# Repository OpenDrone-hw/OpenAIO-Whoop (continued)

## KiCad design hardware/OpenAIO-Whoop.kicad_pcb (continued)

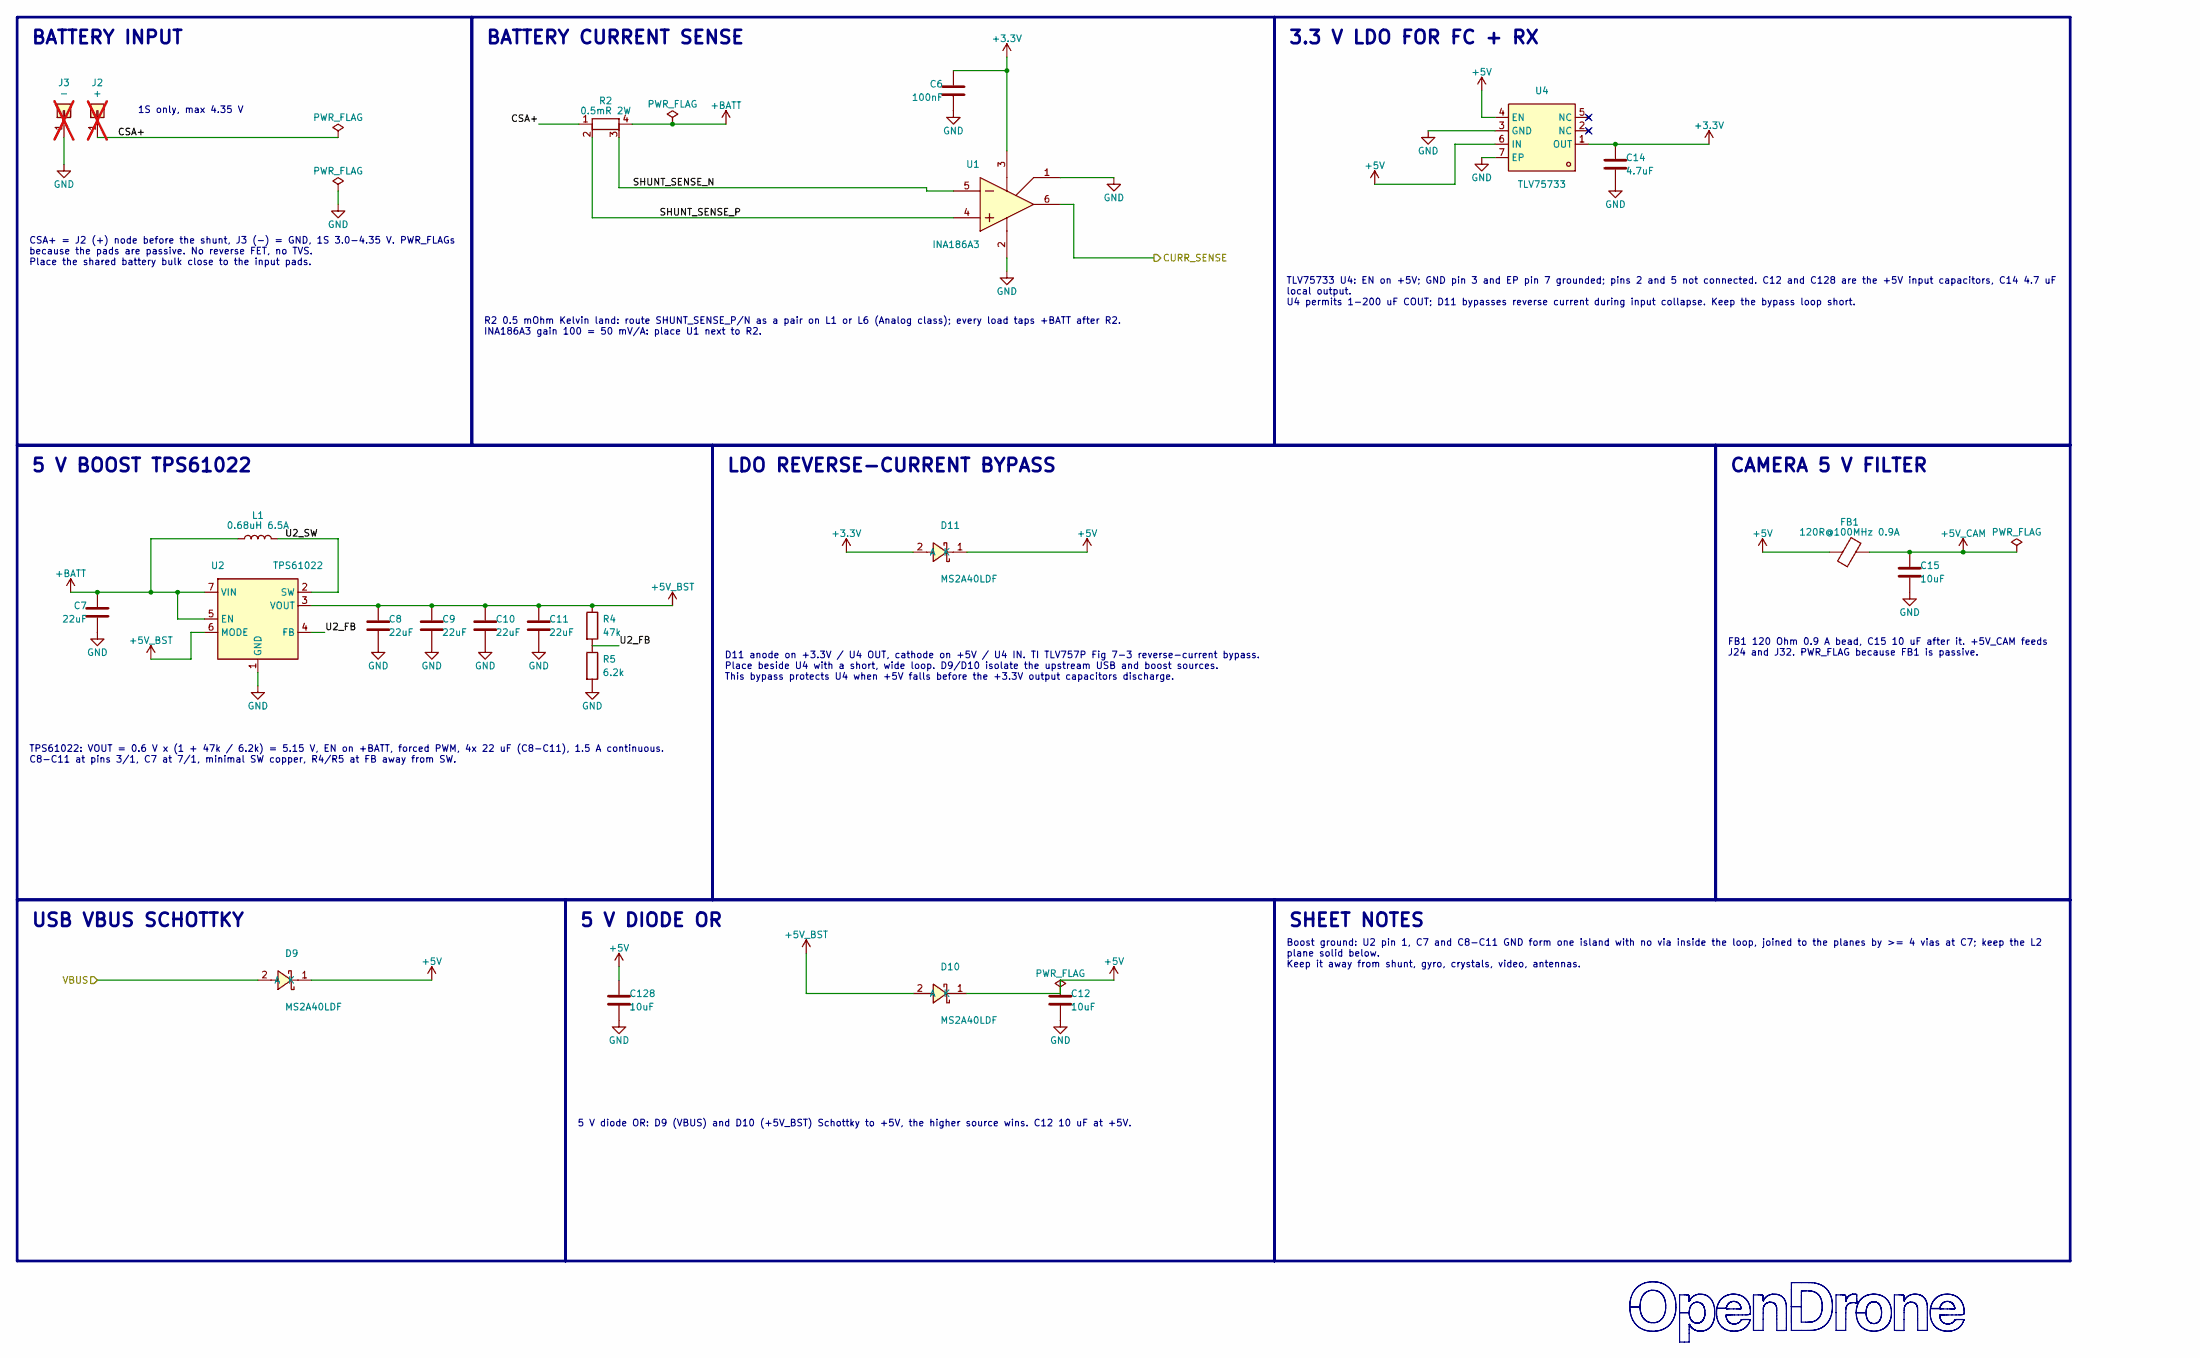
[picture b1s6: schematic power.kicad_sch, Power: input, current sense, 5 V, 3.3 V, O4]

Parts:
C6: 100nF; C_0201_0603Metric_L; MPN GRM033C81E104KE14D; LCSC C181047
C7, C8, C9, C10, C11: 22uF; C_0603_1608Metric_L; MPN GRM188C80J226ME15D; LCSC C393031
C12, C15, C128: 10uF; C_0402_1005Metric_L; MPN GRM155C80J106ME11D; LCSC C237279
C14: 4.7uF; C_0201_0603Metric_L; MPN GRM035R60J475ME15D; LCSC C335103
D9, D10, D11: MS2A40LDF; DFN1610-2_L1.6-W1.0-P1.05-RD; MPN MS2A40LDF; LCSC C7380000
FB1: 120R@100MHz 0.9A; L_0201_0603Metric_L; MPN BLM03PX121SN1D; LCSC C525479
J2: +; BattPad_D1.7mm_PTH1.1; not fitted
J3: -; BattPad_D1.7mm_PTH1.1; not fitted
L1: 0.68uH 6.5A; IND-SMD_L2.5-W2.0_FTC252012_L; MPN FTC252012SR68MBCA; LCSC C5832369
R2: 0.5mR 2W; R_1206_Kelvin_4Pad_NetTie_HCS1206_L; MPN HCS1206FTL500; LCSC C346511
R4: 47k; R_0201_0603Metric_L; MPN RC0201FR-0747KL; LCSC C138139
R5: 6.2k; R_0201_0603Metric_L; MPN RC0201FR-076K2L; LCSC C295814
U1: INA186A3; SOT-363_SC-70-6_Dense; MPN INA186A3IDCKR; LCSC C2058245
U2: TPS61022; TI_VQFN-HR-7_2x2mm_RWU_L; MPN TPS61022RWUR; LCSC C915088
U4: TLV75733; WSON-6-1EP_2x2mm_P0.65mm_EP1x1.6mm_L; MPN TLV75733PDRVR; LCSC C2868428

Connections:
+3.3V: C6.1, C14.1, D11.2 (A), U1.3 (VS), U4.1 (OUT); also elsewhere on the board
+5V: C12.1, C128.1, D9.1 (K), D10.1 (K), D11.1 (K), FB1.1, U4.4 (EN), U4.6 (IN); also elsewhere on the board
+5V_BST: C8.1, C9.1, C10.1, C11.1, D10.2 (A), R4.1, U2.3 (VOUT), U2.6 (MODE); also elsewhere on the board
+5V_CAM: C15.1, FB1.2; also elsewhere on the board
+BATT: C7.1, L1.1, R2.4, U2.5 (EN), U2.7 (VIN); also elsewhere on the board
/CURR_SENSE: U1.6 (OUT); also elsewhere on the board
/POWER/CSA+: J2.1 (Pin_1_1), R2.1
/POWER/SHUNT_SENSE_N: R2.3, U1.5 (-IN)
/POWER/SHUNT_SENSE_P: R2.2, U1.4 (+IN)
/POWER/U2_FB: R4.2, R5.1, U2.4 (FB)
/POWER/U2_SW: L1.2, U2.2 (SW)
/VBUS: D9.2 (A); also elsewhere on the board
GND: C6.2, C7.2, C8.2, C9.2, C10.2, C11.2, C12.2, C14.2, C15.2, C128.2, J3.1 (Pin_1_1), R5.2, U1.1 (REF), U1.2 (GND), U2.1 (GND), U4.3 (GND), U4.7 (EP); also elsewhere on the board

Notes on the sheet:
SHEET NOTES
1S only, max 4.35 V
LDO REVERSE-CURRENT BYPASS
5 V BOOST TPS61022
BATTERY CURRENT SENSE
3.3 V LDO FOR FC + RX
USB VBUS SCHOTTKY
CAMERA 5 V FILTER
5 V DIODE OR
BATTERY INPUT
FB1 120 Ohm 0.9 A bead, C15 10 uF after it. +5V_CAM feeds J24 and J32. PWR_FLAG because FB1 is passive.
Boost ground: U2 pin 1, C7 and C8-C11 GND form one island with no via inside the loop, joined to the planes by >= 4 vias at C7; keep the L2 plane solid below. Keep it away from shunt, gyro, crystals, video, antennas.
CSA+ = J2 (+) node before the shunt, J3 (-) = GND, 1S 3.0-4.35 V. PWR_FLAGs because the pads are passive. No reverse FET, no TVS. Place the shared battery bulk close to the input pads.
5 V diode OR: D9 (VBUS) and D10 (+5V_BST) Schottky to +5V, the higher source wins. C12 10 uF at +5V.
TPS61022: VOUT = 0.6 V x (1 + 47k / 6.2k) = 5.15 V, EN on +BATT, forced PWM, 4x 22 uF (C8-C11), 1.5 A continuous. C8-C11 at pins 3/1, C7 at 7/1, minimal SW copper, R4/R5 at FB away from SW.
R2 0.5 mOhm Kelvin land: route SHUNT_SENSE_P/N as a pair on L1 or L6 (Analog class); every load taps +BATT after R2. INA186A3 gain 100 = 50 mV/A: place U1 next to R2.
TLV75733 U4: EN on +5V; GND pin 3 and EP pin 7 grounded; pins 2 and 5 not connected. C12 and C128 are the +5V input capacitors, C14 4.7 uF local output. U4 permits 1-200 uF COUT; D11 bypasses reverse current during input collapse. Keep the bypass loop short.
D11 anode on +3.3V / U4 OUT, cathode on +5V / U4 IN. TI TLV757P Fig 7-3 reverse-current bypass. Place beside U4 with a short, wide loop. D9/D10 isolate the upstream USB and boost sources. This bypass protects U4 when +5V falls before the +3.3V output capacitors discharge.

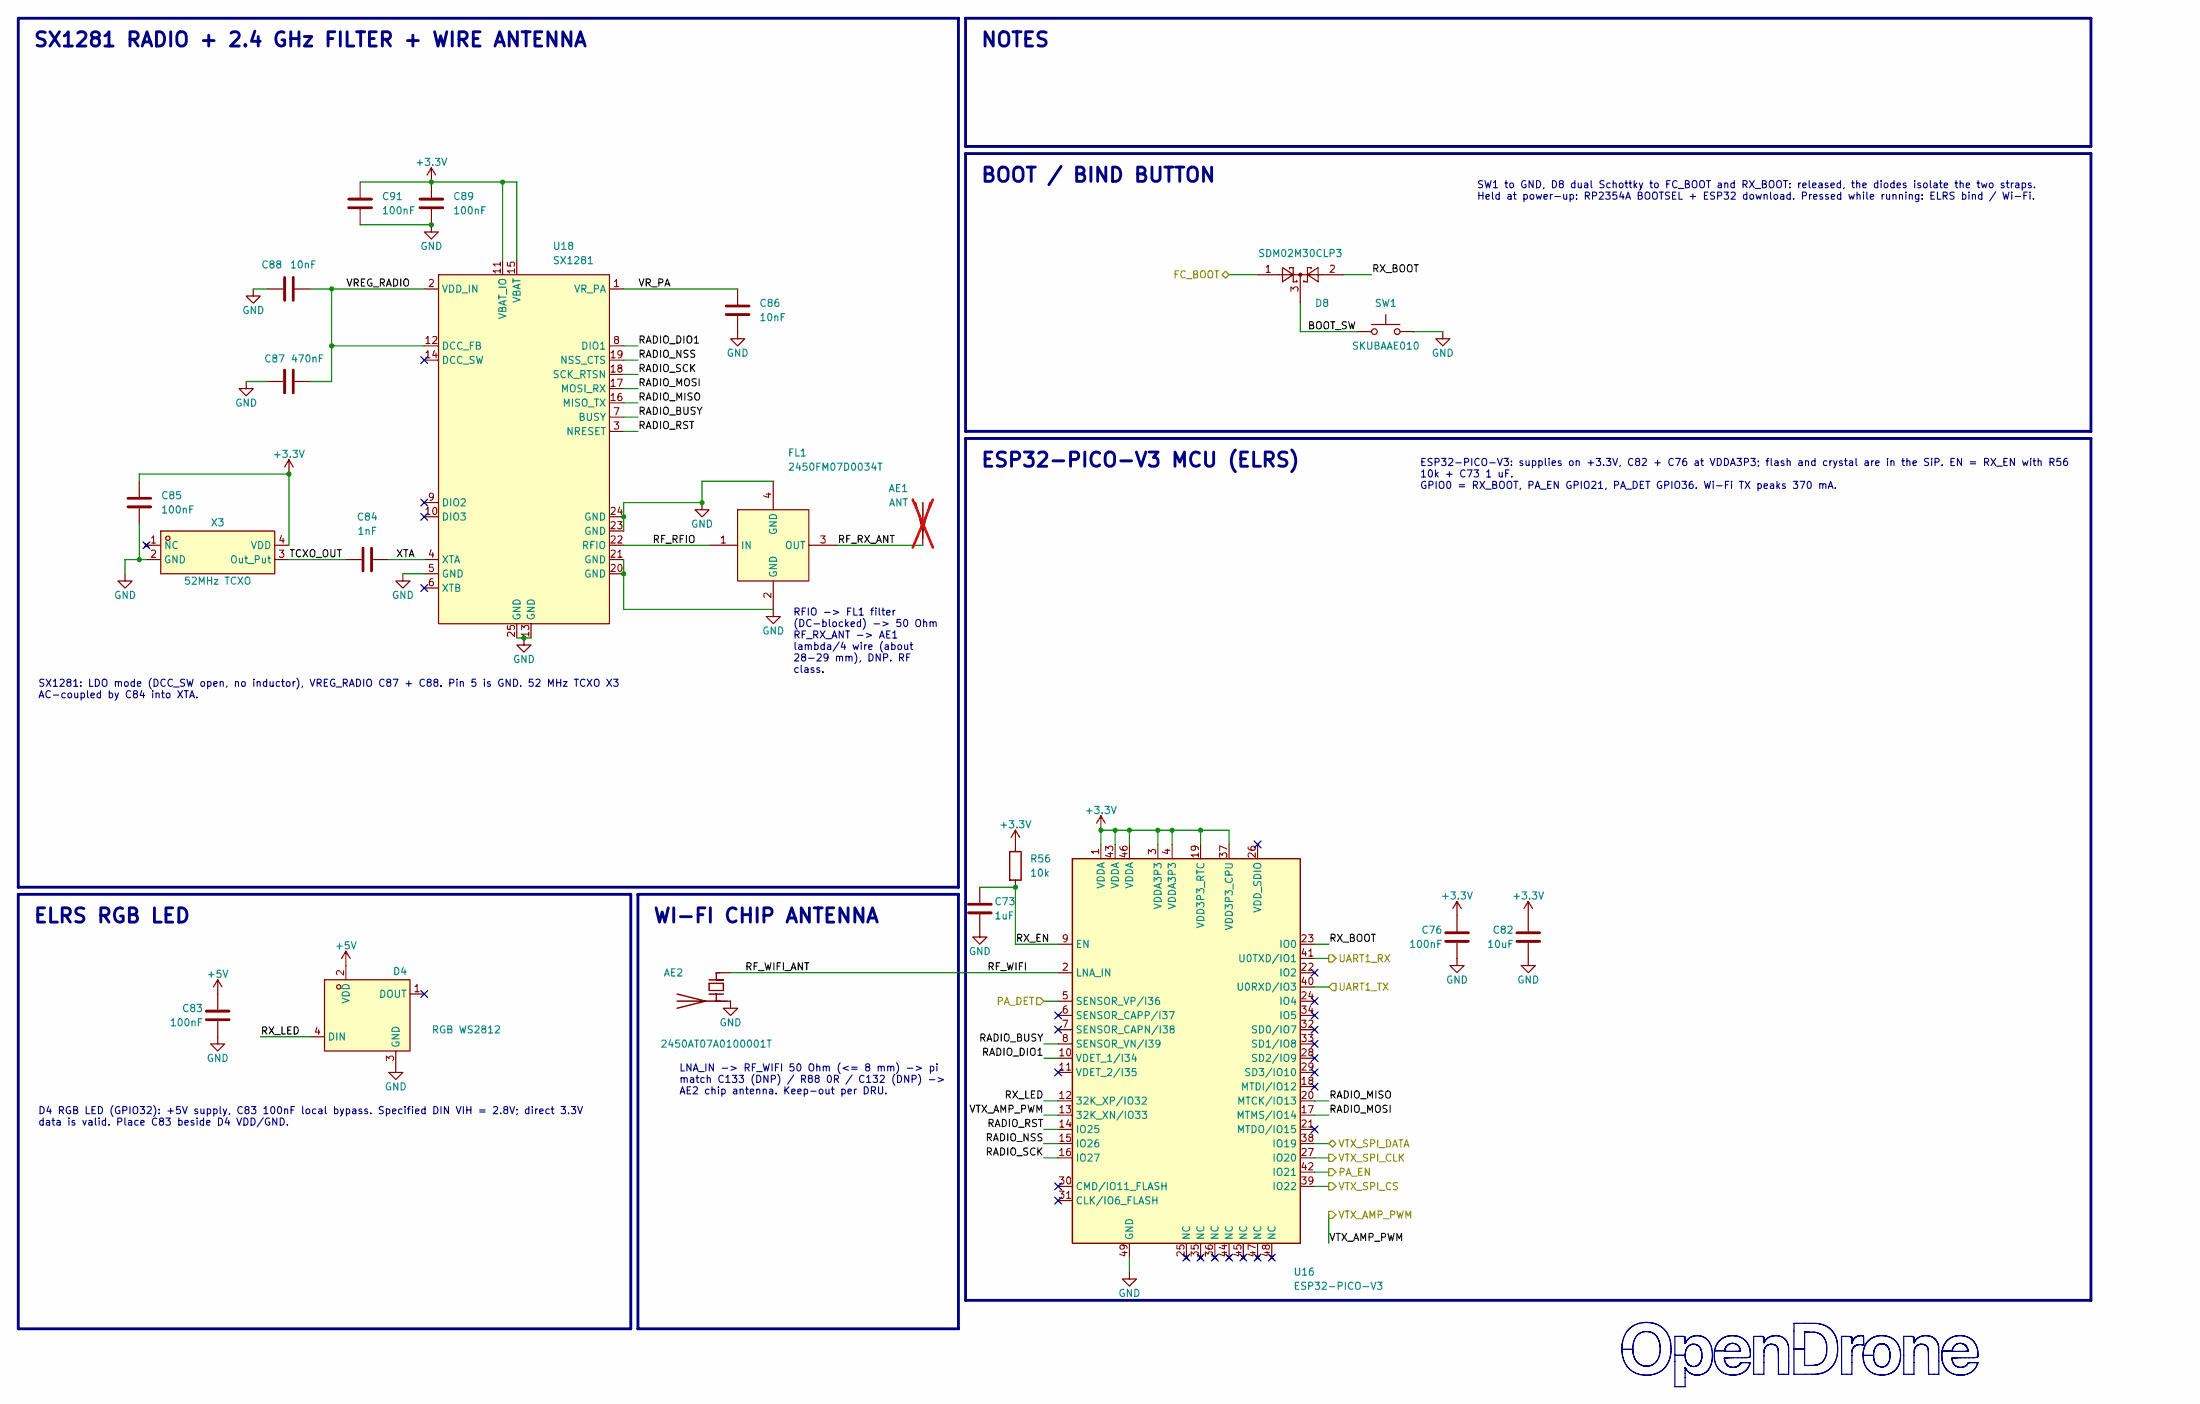
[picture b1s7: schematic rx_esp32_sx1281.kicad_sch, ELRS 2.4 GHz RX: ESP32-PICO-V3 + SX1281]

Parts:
AE1: ANT; AE_WireHole_PTH0.5mm; not fitted
AE2: 2450AT07A0100001T; ANT-SMD_4P-L1.0-W0.5_Johanson_2450AT07A0100; MPN 2450AT07A0100001T; LCSC C17531353
C73: 1uF; C_0201_0603Metric_L; MPN GRM033R61A105ME44D; LCSC C76935
C76, C83, C85, C89, C91: 100nF; C_0201_0603Metric_L; MPN GRM033C81E104KE14D; LCSC C181047
C82: 10uF; C_0402_1005Metric_L; MPN GRM155C80J106ME11D; LCSC C237279
C84: 1nF; C_0201_0603Metric_L; MPN GRM033R71H102KA12D; LCSC C85934
C86, C88: 10nF; C_0201_0603Metric_L; MPN GRM033R71A103KA01D; LCSC C76941
C87: 470nF; C_0201_0603Metric_L; MPN GRM033R60J474KE90D; LCSC C85926
D4: RGB WS2812; LED-SMD_4P-L1.0-W1.0-TL_XL-1010RGBC-WS2812B_Dense; MPN XL-1010RGBC-2812B; LCSC C5349953
D8: SDM02M30CLP3; X2-DFN1006-3_L1.0-W0.6_SDM02M30CLP3; MPN SDM02M30CLP3-7B; LCSC C5244996
FL1: 2450FM07D0034T; FILTER-SMD_4P-L1.0-W0.5-L_W; MPN 2450FM07D0034T; LCSC C2651081
R56: 10k; R_0201_0603Metric_L; MPN RC0201FR-0710KL; LCSC C106225
SW1: SKUBAAE010; SW_Alps_SKUBAAE010_2.4x1.4mm; MPN SKUBAAE010
U16: ESP32-PICO-V3; LGA-48_7x7mm_P0.5mm_EP_ESP32-PICO_L; MPN ESP32-PICO-V3; LCSC C967022
U18: SX1281; QFN-24_L4.0-W4.0-P0.50-TL-EP2.6_L; MPN SX1281IMLTRT; LCSC C2151551
X3: 52MHz TCXO; OSC-SMD_4P-L2.0-W1.6-BL_TXC_7Z_Dense; MPN OW7EL89CENUNFAYLC-52M; LCSC C22434896

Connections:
+3.3V: C76.1, C82.1, C85.1, C89.1, C91.1, R56.1, U16.1 (VDDA), U16.3 (VDDA3P3), U16.4 (VDDA3P3), U16.19 (VDD3P3_RTC), U16.37 (VDD3P3_CPU), U16.43 (VDDA), U16.46 (VDDA), U18.11 (VBAT_IO), U18.15 (VBAT), X3.4 (VDD); also elsewhere on the board
+5V: C83.1, D4.2 (VDD); also elsewhere on the board
/FC_BOOT: D8.1 (A1); also elsewhere on the board
/PA_DET: U16.5 (SENSOR_VP/I36); also elsewhere on the board
/PA_EN: U16.42 (IO21); also elsewhere on the board
/RX/BOOT_SW: D8.3 (K), SW1.1
/RX/RADIO_BUSY: U16.8 (SENSOR_VN/I39), U18.7 (BUSY)
/RX/RADIO_DIO1: U16.10 (VDET_1/I34), U18.8 (DIO1)
/RX/RADIO_MISO: U16.20 (MTCK/IO13), U18.16 (MISO_TX)
/RX/RADIO_MOSI: U16.17 (MTMS/IO14), U18.17 (MOSI_RX)
/RX/RADIO_NSS: U16.15 (IO26), U18.19 (NSS_CTS)
/RX/RADIO_RST: U16.14 (IO25), U18.3 (NRESET)
/RX/RADIO_SCK: U16.16 (IO27), U18.18 (SCK_RTSN)
/RX/RF_RFIO: FL1.1 (IN), U18.22 (RFIO)
/RX/RF_RX_ANT: AE1.1 (A_1), FL1.3 (OUT)
/RX/RF_WIFI: AE2.1 (FEED), AE2.4 (FEED), U16.2 (LNA_IN)
/RX/RX_BOOT: D8.2 (A2), U16.23 (IO0)
/RX/RX_EN: C73.1, R56.2, U16.9 (EN)
/RX/RX_LED: D4.4 (DIN), U16.12 (32K_XP/IO32)
/RX/TCXO_OUT: C84.1, X3.3 (Out_Put)
/RX/VREG_RADIO: C87.2, C88.2, U18.2 (VDD_IN), U18.12 (DCC_FB)
/RX/VR_PA: C86.1, U18.1 (VR_PA)
/RX/XTA: C84.2, U18.4 (XTA)
/UART1_RX: U16.41 (U0TXD/IO1); also elsewhere on the board
/UART1_TX: U16.40 (U0RXD/IO3); also elsewhere on the board
/VTX_AMP_PWM: U16.13 (32K_XN/IO33); also elsewhere on the board
/VTX_SPI_CLK: U16.27 (IO20); also elsewhere on the board
/VTX_SPI_CS: U16.39 (IO22); also elsewhere on the board
/VTX_SPI_DATA: U16.38 (IO19); also elsewhere on the board
GND: AE2.2 (GND), AE2.3 (GND), C73.2, C76.2, C82.2, C83.2, C85.2, C86.2, C87.1, C88.1, C89.2, C91.2, D4.3 (GND), FL1.2 (GND), FL1.4 (GND), SW1.2, U16.49 (GND), U18.5 (GND), U18.13 (GND), U18.20 (GND), U18.21 (GND), U18.23 (GND), U18.24 (GND), U18.25 (GND), X3.2 (GND); also elsewhere on the board

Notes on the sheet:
NOTES
ELRS RGB LED
ESP32-PICO-V3 MCU (ELRS)
SX1281 RADIO + 2.4 GHz FILTER + WIRE ANTENNA
WI-FI CHIP ANTENNA
BOOT / BIND BUTTON
RFIO -> FL1 filter (DC-blocked) -> 50 Ohm RF_RX_ANT -> AE1 lambda/4 wire (about 28-29 mm), DNP. RF class.
SW1 to GND, D8 dual Schottky to FC_BOOT and RX_BOOT: released, the diodes isolate the two straps. Held at power-up: RP2354A BOOTSEL + ESP32 download. Pressed while running: ELRS bind / Wi-Fi.
ESP32-PICO-V3: supplies on +3.3V, C82 + C76 at VDDA3P3; flash and crystal are in the SiP. EN = RX_EN with R56 10k + C73 1 uF. GPIO0 = RX_BOOT, PA_EN GPIO21, PA_DET GPIO36. Wi-Fi TX peaks 370 mA.
SX1281: LDO mode (DCC_SW open, no inductor), VREG_RADIO C87 + C88. Pin 5 is GND. 52 MHz TCXO X3 AC-coupled by C84 into XTA.
LNA_IN -> RF_WIFI 50 Ohm (<= 8 mm) -> pi match C133 (DNP) / R88 0R / C132 (DNP) -> AE2 chip antenna. Keep-out per DRU.
D4 RGB LED (GPIO32): +5V supply, C83 100nF local bypass. Specified DIN VIH = 2.8V; direct 3.3V data is valid. Place C83 beside D4 VDD/GND.

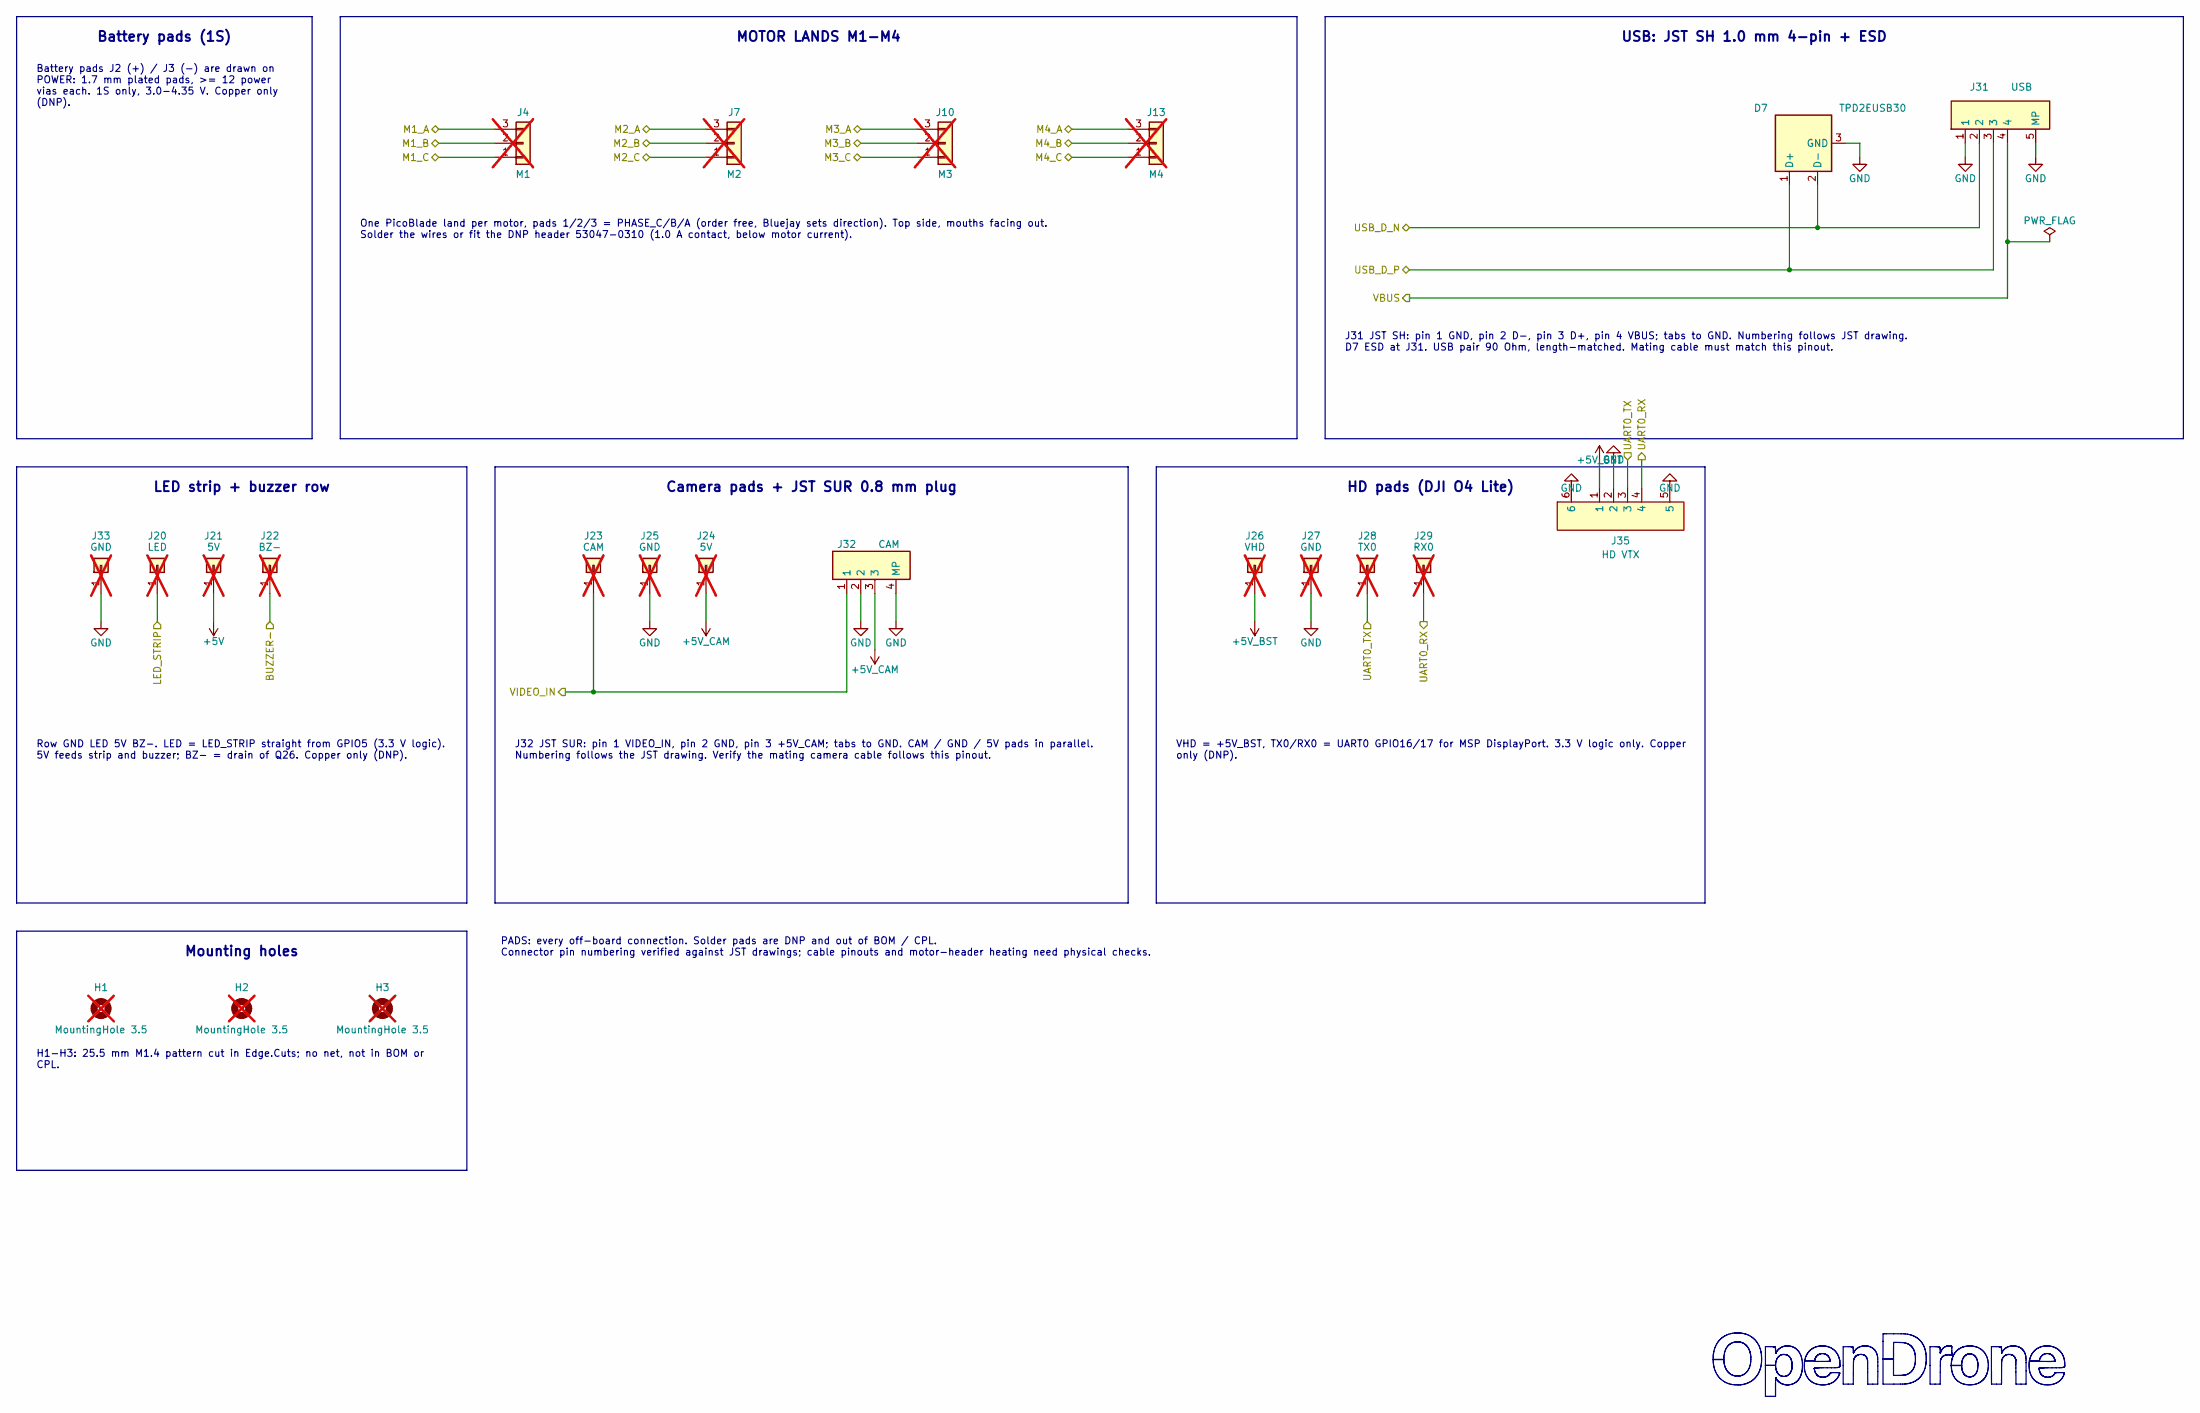
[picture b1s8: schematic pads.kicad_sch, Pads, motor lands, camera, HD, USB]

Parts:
D7: TPD2EUSB30; TI_SOT-9X3-3_DRT_L; MPN TPD2EUSB30DRTR; LCSC C97502
H1, H2, H3: MountingHole 3.5; MountingHole_3.5mm_Ear_Flange5.2; not fitted
J4: M1; MotorPad_PicoBlade_1x03_P1.25mm_PTH0.5; MPN 53047-0310; not fitted
J7: M2; MotorPad_PicoBlade_1x03_P1.25mm_PTH0.5; MPN 53047-0310; not fitted
J10: M3; MotorPad_PicoBlade_1x03_P1.25mm_PTH0.5; MPN 53047-0310; not fitted
J13: M4; MotorPad_PicoBlade_1x03_P1.25mm_PTH0.5; MPN 53047-0310; not fitted
J20: LED; SolderPad_1.0x1.2mm; not fitted
J21, J24: 5V; SolderPad_1.0x1.2mm; not fitted
J22: BZ-; SolderPad_1.0x1.2mm; not fitted
J23: CAM; SolderPad_1.0x1.2mm; not fitted
J25, J27, J33: GND; SolderPad_1.0x1.2mm; not fitted
J26: VHD; SolderPad_1.0x1.2mm; not fitted
J28: TX0; SolderPad_1.0x1.2mm; not fitted
J29: RX0; SolderPad_1.0x1.2mm; not fitted
J31: USB; CONN-SMD_4P-P1.00_BM04B-SRSS-TB; MPN BM04B-SRSS-TB(LF)(SN); LCSC C160390
J32: CAM; JST_SUR_SM03B-SURS-TF_1x03-1MP_P0.80mm_Horizontal; MPN SM03B-SURS-TF(LF)(SN); LCSC C265338
J35: HD VTX; CONN-SMD_4P-P1.00_SM04B-SRSS-TB-LF-SN; MPN SM04B-SRSS-TB(LF)(SN); LCSC C160404

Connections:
+5V: J21.1 (Pin_1_1); also elsewhere on the board
+5V_BST: J26.1 (Pin_1_1), J35.1; also elsewhere on the board
+5V_CAM: J24.1 (Pin_1_1), J32.3; also elsewhere on the board
/BUZZER-: J22.1 (Pin_1_1); also elsewhere on the board
/ESC1/PHASE_A: J4.3; also elsewhere on the board
/ESC1/PHASE_B: J4.2; also elsewhere on the board
/ESC1/PHASE_C: J4.1; also elsewhere on the board
/ESC2/PHASE_A: J7.3; also elsewhere on the board
/ESC2/PHASE_B: J7.2; also elsewhere on the board
/ESC2/PHASE_C: J7.1; also elsewhere on the board
/ESC3/PHASE_A: J10.3; also elsewhere on the board
/ESC3/PHASE_B: J10.2; also elsewhere on the board
/ESC3/PHASE_C: J10.1; also elsewhere on the board
/ESC4/PHASE_A: J13.3; also elsewhere on the board
/ESC4/PHASE_B: J13.2; also elsewhere on the board
/ESC4/PHASE_C: J13.1; also elsewhere on the board
/LED_STRIP: J20.1 (Pin_1_1); also elsewhere on the board
/UART0_RX: J29.1 (Pin_1_1), J35.4; also elsewhere on the board
/UART0_TX: J28.1 (Pin_1_1), J35.3; also elsewhere on the board
/USB_D_N: D7.2 (D-), J31.2; also elsewhere on the board
/USB_D_P: D7.1 (D+), J31.3; also elsewhere on the board
/VBUS: J31.4; also elsewhere on the board
/VIDEO_IN: J23.1 (Pin_1_1), J32.1; also elsewhere on the board
GND: D7.3 (GND), J25.1 (Pin_1_1), J27.1 (Pin_1_1), J31.1, J31.5 (MP), J31.6 (MP), J32.2, J32.4 (MP), J32.5 (MP), J33.1 (Pin_1_1), J35.2, J35.5, J35.6; also elsewhere on the board

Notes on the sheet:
Mounting holes
MOTOR LANDS M1-M4
Battery pads (1S)
USB: JST SH 1.0 mm 4-pin + ESD
LED strip + buzzer row
Camera pads + JST SUR 0.8 mm plug
HD pads (DJI O4 Lite)
J32 JST SUR: pin 1 VIDEO_IN, pin 2 GND, pin 3 +5V_CAM; tabs to GND. CAM / GND / 5V pads in parallel. Numbering follows the JST drawing. Verify the mating camera cable follows this pinout.
H1-H3: 25.5 mm M1.4 pattern cut in Edge.Cuts; no net, not in BOM or CPL.
J31 JST SH: pin 1 GND, pin 2 D-, pin 3 D+, pin 4 VBUS; tabs to GND. Numbering follows JST drawing. D7 ESD at J31. USB pair 90 Ohm, length-matched. Mating cable must match this pinout.
VHD = +5V_BST, TX0/RX0 = UART0 GPIO16/17 for MSP DisplayPort. 3.3 V logic only. Copper only (DNP).
Row GND LED 5V BZ-. LED = LED_STRIP straight from GPIO5 (3.3 V logic). 5V feeds strip and buzzer; BZ- = drain of Q26. Copper only (DNP).
Battery pads J2 (+) / J3 (-) are drawn on POWER: 1.7 mm plated pads, >= 12 power vias each. 1S only, 3.0-4.35 V. Copper only (DNP).
One PicoBlade land per motor, pads 1/2/3 = PHASE_C/B/A (order free, Bluejay sets direction). Top side, mouths facing out. Solder the wires or fit the DNP header 53047-0310 (1.0 A contact, below motor current).
PADS: every off-board connection. Solder pads are DNP and out of BOM / CPL. Connector pin numbering verified against JST drawings; cable pinouts and motor-header heating need physical checks.

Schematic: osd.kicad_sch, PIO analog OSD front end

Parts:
C66: 100pF; C_0201_0603Metric_L; MPN GRM0335C1H101JA01D; LCSC C76922
C67: 470pF; C_0201_0603Metric_L; MPN CC0201JRX7R9BB471; LCSC C526944
C68: 1uF; C_0201_0603Metric_L; MPN GRM033R61A105ME44D; LCSC C76935
C70, C71: 100nF; C_0201_0603Metric_L; MPN GRM033C81E104KE14D; LCSC C181047
D3: SDM02U30LP3; X3-DFN0603-2_L0.6-W0.3-RD_W; MPN SDM02U30LP3-7B; LCSC C151629
R51: 75R; R_0201_0603Metric_L; MPN RC0201FR-0775RL; LCSC C274878
R52: 820R; R_0201_0603Metric_L; MPN RC0201FR-07820RL; LCSC C155736
R53: 2.4k; R_0201_0603Metric_L; MPN RTT012401FTH; LCSC C166281
R54: 270R; R_0201_0603Metric_L; MPN RC0201FR-07270RL; LCSC C295793
R55: 680R; R_0201_0603Metric_L; MPN RC0201FR-07680RL; LCSC C274876
U14: SN74LVC1G3157; X2SON-6_L1.0-W0.8-BL_Dense; MPN SN74LVC1G3157DTBR; LCSC C2673087
U15: TLV7031; X2SON-4_L0.8-W0.8-P0.48-TL-A_Dense; MPN TLV7031DPWR; LCSC C2876045

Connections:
+3.3V: C70.1, C71.1, R53.2, U14.5 (VCC), U15.2 (V+); also elsewhere on the board
/OSD/OSD_LVL: R52.2, R53.1, R54.2, U14.1 (B2)
/OSD/VID_DC: C68.2, D3.1 (C), U15.5 (IN+)
/OSD/VID_FILT: C67.1, C68.1, R55.1
/OSD_EN: U14.6 (S); also elsewhere on the board
/OSD_SYNC: U15.1 (OUT); also elsewhere on the board
/OSD_W: R52.1; also elsewhere on the board
/VIDEO_IN: C66.1, R51.1, R55.2, U14.3 (B1); also elsewhere on the board
/VIDEO_OUT: U14.4 (A); also elsewhere on the board
GND: C66.2, C67.2, C70.2, C71.2, D3.2 (A), R51.2, R54.1, U14.2 (GND), U15.3 (V-), U15.4 (IN-); also elsewhere on the board

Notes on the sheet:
OSD_EN
OSD_W selects white (high) or black (low) through the divider
Analog switch
OSD_W
VIDEO PATH
black pixel
U15 V+ (2) is decoupled by C70, shared with U14
Sync detection: sync tips clamped to -VF
transparent
Chroma Filter fc = 500 kHz
S low (OSD_EN low / reset): B1 camera S high: B2 OSD level
75R input termination 100p entry shunt
white pixel
DC Restoration
Comparator: OSD_SYNC low during sync (GPIO23, PIO2)
C70 is the one supply cap of U14 and U15: place it between them. R51/C66 at the CAM pad line; video on L1/L6 over GND, away from the boost.
OSD_EN low (reset): camera passes through. OSD_EN high: OSD_W high = white, low = black. No OSD without camera sync. OSD_W/EN/SYNC = GPIO21/22/23 (PIO2).
VIDEO_OUT drives the VTX video network directly. Loaded levels: black about 0.23 V, white about 0.89 V.

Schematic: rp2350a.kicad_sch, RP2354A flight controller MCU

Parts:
C42, C44, C45, C46, C47, C48, C49, C50, C51, C54, C59, C60: 100nF; C_0201_0603Metric_L; MPN GRM033C81E104KE14D; LCSC C181047
C52: 4.7uF; C_0201_0603Metric_L; MPN GRM035R60J475ME15D; LCSC C335103
C56, C57, C58: 4.7uF; C_0402_1005Metric_L; MPN CL05A475MP5NRNC; LCSC C23733
L2: 3.3uH; IND-SMD_L2.0-W1.6_AOTA-B201610S3R3-101-T_Dense; MPN AOTA-B201610S3R3-101-T; LCSC C42411119
Q26: AP1606; DFN-3L_L1.0-W0.6-P0.65-BR_W; MPN AP1606; LCSC C2849580
R41, R42, R43: 27R; R_0201_0603Metric_L; MPN RC0201FR-0727RL; LCSC C273268
R44, R47, R57, R67, R69, R70: 1k; R_0201_0603Metric_L; MPN RC0201FR-071KL; LCSC C138165
R45, R46: 10k; R_0201_0603Metric_L; MPN RC0201FR-0710KL; LCSC C106225
R48: 100k; R_0201_0603Metric_L; MPN RC0201FR-07100KL; LCSC C106224
TP12: CLK; TestPoint_Pad_D0.30mm_MicroVia_L
TP13: DIO; TestPoint_Pad_D0.30mm_MicroVia_L
U10: RP2354A; QFN-60_L7.0-W7.0-P0.40-TL-EP3.4_L; MPN RP2354A; LCSC C41378174
X1: 12MHz; OSC-SMD_4P-L2.0-W1.6-BL_YXC_YSO110TR_Dense; MPN OT201612MJBA4SL; LCSC C669076

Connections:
+1.1V: C50.1, C51.1, C52.1, C56.1, L2.1, U10.6 (DVDD), U10.23 (DVDD), U10.39 (DVDD), U10.50 (VREG_FB)
+3.3V: C42.1, C44.1, C45.1, C46.1, C47.1, C48.1, C49.1, C54.1, C58.1, R41.1, U10.1 (IOVDD), U10.11 (IOVDD), U10.20 (IOVDD), U10.26 (RUN), U10.30 (IOVDD), U10.38 (IOVDD), U10.44 (ADC_AVDD), U10.45 (IOVDD), U10.49 (VREG_VIN), U10.53 (USB_OTP_VDD), U10.54 (QSPI_IOVDD), X1.1 (EN), X1.4 (VDD); also elsewhere on the board
+BATT: R45.2; also elsewhere on the board
/BUZZER-: Q26.3 (D); also elsewhere on the board
/CURR_SENSE: R47.1; also elsewhere on the board
/FC_BOOT: R44.2; also elsewhere on the board
/FLASH_CS: U10.3 (GPIO1); also elsewhere on the board
/GYRO_CLKIN: U10.17 (GPIO13); also elsewhere on the board
/GYRO_CS: U10.19 (GPIO15); also elsewhere on the board
/GYRO_INT: U10.10 (GPIO7); also elsewhere on the board
/HD_EN: U10.31 (GPIO19); also elsewhere on the board
/LED0: U10.14 (GPIO10); also elsewhere on the board
/LED1: U10.36 (GPIO24); also elsewhere on the board
/LED_STRIP: U10.8 (GPIO5); also elsewhere on the board
/MOTOR1: R69.1; also elsewhere on the board
/MOTOR2: R70.2; also elsewhere on the board
/MOTOR3: R57.1; also elsewhere on the board
/MOTOR4: R67.2; also elsewhere on the board
/OSD_EN: U10.34 (GPIO22); also elsewhere on the board
/OSD_SYNC: U10.35 (GPIO23); also elsewhere on the board
/OSD_W: U10.33 (GPIO21); also elsewhere on the board
/RP2350A/ADC_CURR: C60.1, R47.2, U10.40 (GPIO26_ADC0)
/RP2350A/ADC_VBAT: C59.2, R45.1, R46.2, U10.41 (GPIO27_ADC1)
/RP2350A/BEEPER: Q26.1 (G), R48.2, U10.37 (GPIO25)
/RP2350A/QSPI_SS: R44.1, U10.60 (QSPI_SS)
/RP2350A/SWCLK: TP12.1 (1_1), U10.24 (SWCLK)
/RP2350A/SWDIO: TP13.1 (1_1), U10.25 (SWDIO)
/RP2350A/U10_USB_D_N: R43.2, U10.51 (USB_DM)
/RP2350A/U10_USB_D_P: R42.1, U10.52 (USB_DP)
/RP2350A/VREG_AVDD: C57.1, R41.2, U10.46 (VREG_AVDD)
/RP2350A/VREG_LX: L2.2, U10.48 (VREG_LX)
/RP2350A/XIN: U10.21 (XIN), X1.3 (OUT)
/SPI0_MISO: U10.2 (GPIO0); also elsewhere on the board
/SPI0_MOSI: U10.5 (GPIO3); also elsewhere on the board
/SPI0_SCK: U10.4 (GPIO2); also elsewhere on the board
/SPI1_MISO: U10.16 (GPIO12); also elsewhere on the board
/SPI1_MOSI: U10.15 (GPIO11); also elsewhere on the board
/SPI1_SCK: U10.18 (GPIO14); also elsewhere on the board
/UART0_RX: U10.28 (GPIO17); also elsewhere on the board
/UART0_TX: U10.27 (GPIO16); also elsewhere on the board
/UART1_RX: U10.13 (GPIO9); also elsewhere on the board
/UART1_TX: U10.12 (GPIO8); also elsewhere on the board
/USB_D_N: R43.1; also elsewhere on the board
/USB_D_P: R42.2; also elsewhere on the board
GND: C42.2, C44.2, C45.2, C46.2, C47.2, C48.2, C49.2, C50.2, C51.2, C52.2, C54.2, C56.2, C57.2, C58.2, C59.1, C60.2, Q26.2 (S), R46.1, R48.1, U10.47 (VREG_PGND), U10.61 (EP), X1.2 (GND); also elsewhere on the board
unnamed: R69.2, U10.7 (GPIO4)
unnamed: R70.1, U10.9 (GPIO6)
unnamed: R57.2, U10.29 (GPIO18)
unnamed: R67.1, U10.32 (GPIO20)
SBUS: U10.43 (GPIO29_ADC3)

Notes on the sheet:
current sense RC, 1.6 kHz
decoupling caps close to the IC
Boot strap + SWD test vias
in-package flash on QSPI: SD0-SD3, SCLK no-connect
vbat sense, 1/2 scale
buzzer with N-MOS low side switch
RP2354A: in-package flash
12 MHz CMOS oscillator on XIN, XOUT open
SPI0 blackbox GPIO0-3. SPI1 gyro 11/12/14, CS 15, INT 7, CLKIN 13. UART1 8/9 CRSF, UART0 16/17 TX0/RX0 pads. DShot 4/6/18/20. LED 5/10/24, BEEPER 25, HD_EN 19, OSD 21-23, ADC 26/27, GPIO28/29 NC.
R44 1k QSPI_SS -> FC_BOOT: SW1 (RX sheet) pulls it low through D8 = BOOTSEL. Keep the QSPI_SS-to-R44 stub <= 1 mm. TP9, TP12, TP13: filled test vias.
100 nF 0201 per supply pin; C49 at ADC_AVDD 44, C54 <= 1 mm from QSPI_IOVDD 54.
X1 12 MHz CMOS oscillator on XIN (pin 21), XOUT open. C42 at X1 VDD; X1 within 3 mm of pin 21.
R42/R43 27R within 1-2 mm of pins 52/51. USB_D_P/N: 90 Ohm pair over solid GND, length-matched.
Q26 AP1606 buzzer low-side switch: GPIO25 high = on. R48 100k holds it off through reset.
1.1 V SMPS per RP2350 DS 6.3.8: C58, L2, C56 within 3 mm of pins 49/48/50/46; VREG_FB from the C56 pad, one-point GND to VREG_PGND, no copper under L2 on the next layer. L2 pin 2 = VREG_LX; C52 4.7uF directly at DVDD pin 23. C56 + C52 = 9.4uF nominal bulk; C50/C51 = 100nF each.
VBAT: R45/R46 10k/10k, 4.35 V -> 2.18 V on GPIO27. CURR: R47 1k + C60 100 nF on GPIO26.

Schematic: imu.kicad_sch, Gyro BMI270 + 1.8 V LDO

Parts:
C61, C62: 4.7uF; C_0201_0603Metric_L; MPN GRM035R60J475ME15D; LCSC C335103
C137, C138: 100nF; C_0201_0603Metric_L; MPN GRM033C81E104KE14D; LCSC C181047
R49: 10k; R_0201_0603Metric_L; MPN RC0201FR-0710KL; LCSC C106225
U11: BMI270; LGA-14_L3.0-W2.5-P0.50-BR_W; MPN BMI270; LCSC C2836813
U12: TPS7A2018; X2SON-4_L1.0-W1.0-P0.65-TL-EP_Dense; MPN TPS7A2018PDQNRM3; LCSC C36996449

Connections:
+1.8V_GYRO: C62.1, C138.1, U11.8 (VDD), U12.1 (OUT)
+3.3V: C61.1, C137.1, R49.2, U11.5 (VDDIO), U12.3 (EN), U12.4 (IN); also elsewhere on the board
/GYRO_CLKIN: U11.9 (INT2); also elsewhere on the board
/GYRO_CS: R49.1, U11.12 (CSB); also elsewhere on the board
/GYRO_INT: U11.4 (INT1); also elsewhere on the board
/SPI1_MISO: U11.1 (SDO); also elsewhere on the board
/SPI1_MOSI: U11.14 (SDx); also elsewhere on the board
/SPI1_SCK: U11.13 (SCx); also elsewhere on the board
GND: C61.2, C62.2, C137.2, C138.2, U11.6 (GNDIO), U11.7 (GND), U12.2 (GND), U12.5 (EP); also elsewhere on the board

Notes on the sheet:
IMU: BMI270 / ICM-42688-P LGA-14 land
BMI270 fitted: VDDIO +3.3V, VDD +1.8V_GYRO. ASDx/ASCx and OCSB/OSDO no-connect. R49 holds CSB high. ICM-42688-P uses the same land; requires its own decoupling population and firmware sensor/clock setup.
BMI270 local bypass: 100nF per supply pin. For ICM-42688-P: use 10nF on VDDIO and 100nF + 2.2uF on VDD; keep the LDO output capacitor.
U12: C61 at IN and C62 at OUT. C62 must retain >= 0.47uF effective capacitance. C137 directly at U11 VDDIO pin 5; C138 directly at VDD pin 8. Short supply/ground loops to the adjacent plane.

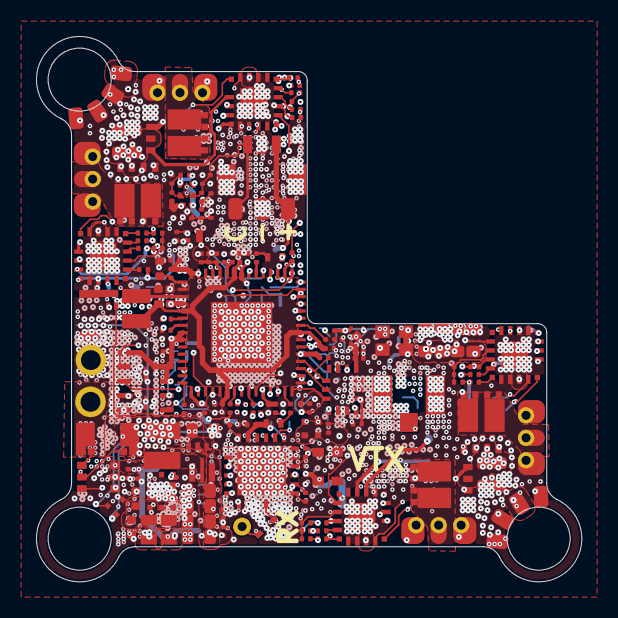
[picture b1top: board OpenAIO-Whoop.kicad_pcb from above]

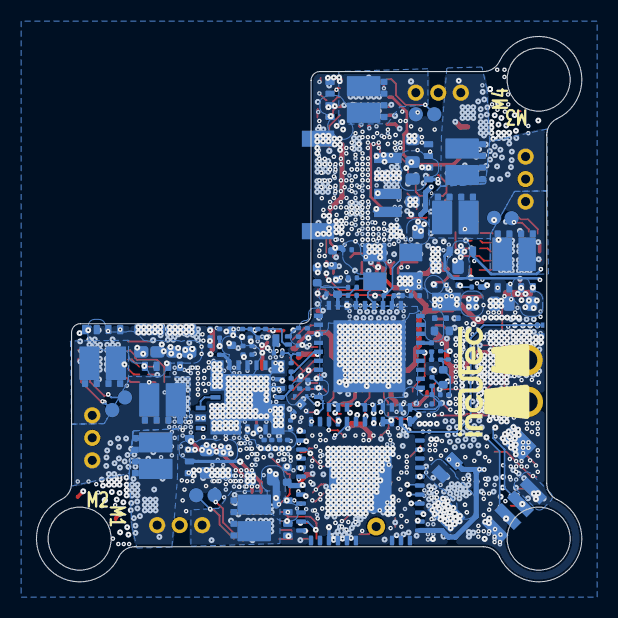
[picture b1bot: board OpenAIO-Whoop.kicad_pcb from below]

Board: 8 copper layers, 30.3 x 30.3 mm, 249 parts (91 on the bottom side), 177 nets.

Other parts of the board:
LOGO1: incutec; incutec_logo_6.1x1.4mm
